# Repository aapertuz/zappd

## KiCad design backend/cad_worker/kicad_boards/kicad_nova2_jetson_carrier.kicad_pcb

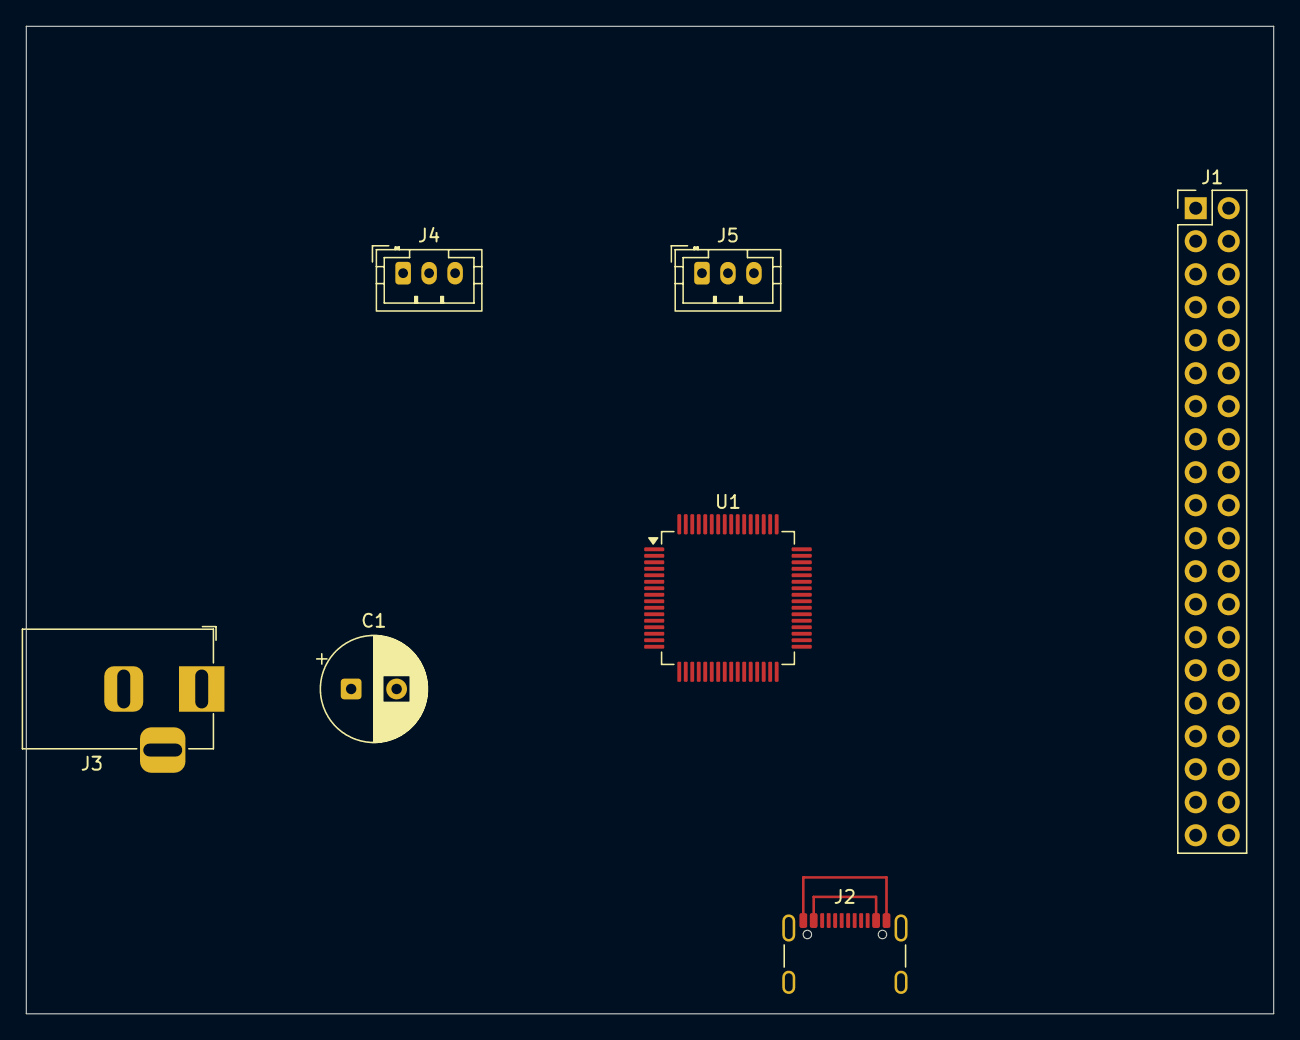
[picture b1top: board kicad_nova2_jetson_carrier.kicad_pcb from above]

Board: 2 copper layers, 96.0 x 76.0 mm, 7 parts (0 on the bottom side), 2 nets.

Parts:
C1: CP_Radial_D8.0mm_P3.50mm
J1: PinHeader_2x20_P2.54mm_Vertical
J2: USB_C_Receptacle_GCT_USB4105-xx-A_16P_TopMnt_Hori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; USB_C_Receptacle_GCT_USB4105-xx-A_16P_TopMnt_Horizontal
J3: BarrelJack_Horizontal
J4, J5: JST_PH_B3B-PH-K_1x03_P2.00mm_Vertical
U1: LQFP-64_10x10mm_P0.5mm

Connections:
GND: J2.A1, J2.A12, J2.B1, J2.B12
VBUS: J2.A4, J2.A9, J2.B4, J2.B9

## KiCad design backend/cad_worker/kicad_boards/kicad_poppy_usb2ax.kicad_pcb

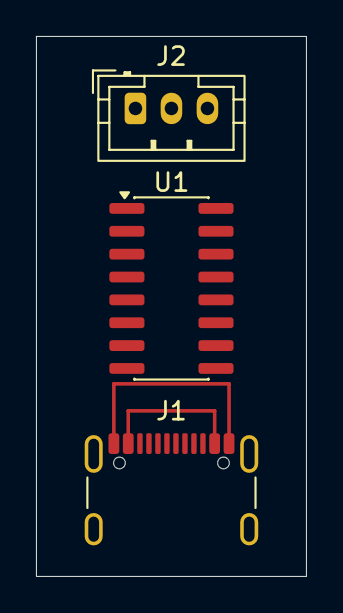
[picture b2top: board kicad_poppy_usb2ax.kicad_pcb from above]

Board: 2 copper layers, 15.0 x 30.0 mm, 3 parts (0 on the bottom side), 2 nets.

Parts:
J1: USB_C_Receptacle_GCT_USB4105-xx-A_16P_TopMnt_Hori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; USB_C_Receptacle_GCT_USB4105-xx-A_16P_TopMnt_Horizontal
J2: JST_PH_B3B-PH-K_1x03_P2.00mm_Vertical
U1: SOIC-16_3.9x9.9mm_P1.27mm

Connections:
GND: J1.A1, J1.A12, J1.B1, J1.B12
VBUS: J1.A4, J1.A9, J1.B4, J1.B9
